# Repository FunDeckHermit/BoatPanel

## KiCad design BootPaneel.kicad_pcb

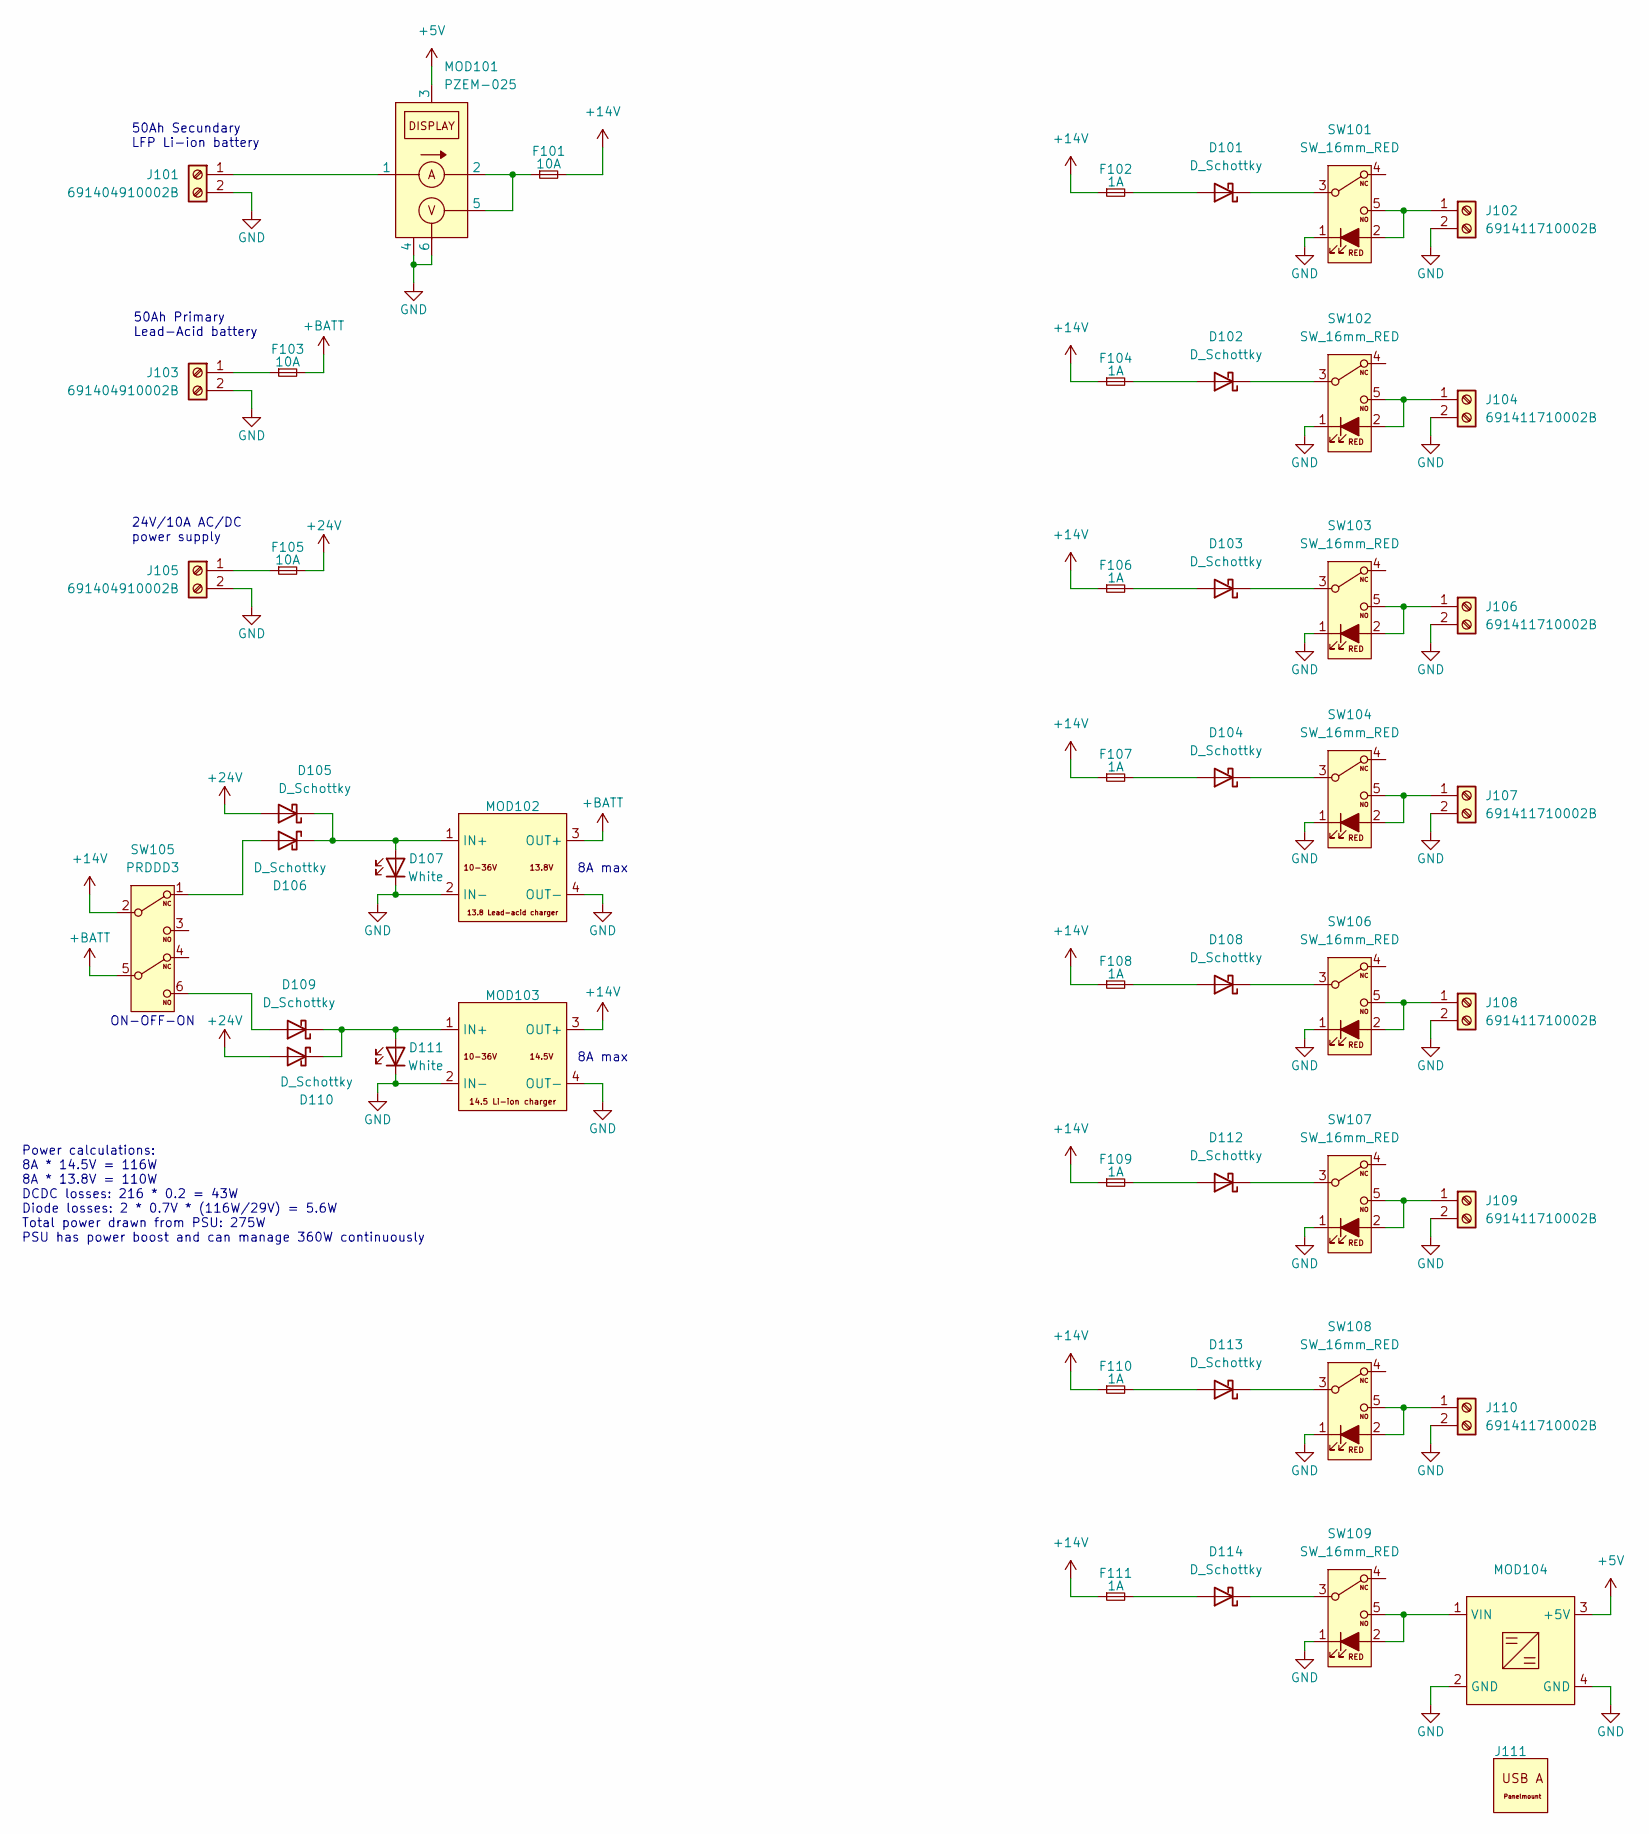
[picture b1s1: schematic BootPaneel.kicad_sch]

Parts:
D101, D102, D103, D104, D105, D106, D108, D109, D110, D112, D113, D114: D_Schottky; D_DO-201AD_P15.24mm_Horizontal
D107, D111: White; LED_Indictor-8mm
F101, F103, F105: 10A; FuseHolder_Regular
F102, F104, F106, F107, F108, F109, F110, F111: 1A; FuseHolder_Regular
J101, J103, J105: 691404910002B
J102, J104, J106, J107, J108, J109, J110: 691411710002B
J111: USBA-PanelMount
MOD101: PZEM-025; DISP_PZEM-025
MOD102, MOD103: MOD_DCDC_14.5V-CHG
MOD104: MOD_BUCK_5V3A
SW101, SW102, SW103, SW104, SW106, SW107, SW108, SW109: SW_16mm_RED; SW_16mm_ILUM
SW105: PRDDD3; SW_PRDDD3

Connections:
+5V: MOD101.3, MOD104.3 (+5V)
+14V: F101.2, F102.1, F104.1, F106.1, F107.1, F108.1, F109.1, F110.1, F111.1, MOD103.3 (OUT+), SW105.2 (C)
+24V: D105.2 (A), D110.2 (A), F105.2
+BATT: F103.2, MOD102.3 (OUT+), SW105.5 (C)
GND: D107.1 (K), D111.1 (K), J101.2, J102.2, J103.2, J104.2, J105.2, J106.2, J107.2, J108.2, J109.2, J110.2, MOD101.4, MOD101.6, MOD102.2 (IN-), MOD102.4 (OUT-), MOD103.2 (IN-), MOD103.4 (OUT-), MOD104.2 (GND), MOD104.4 (GND), SW101.1 (+), SW102.1 (+), SW103.1 (+), SW104.1 (+), SW106.1 (+), SW107.1 (+), SW108.1 (+), SW109.1 (+)
unnamed: D101.2 (A), F102.2
unnamed: D101.1 (K), SW101.3 (C)
unnamed: D102.2 (A), F104.2
unnamed: D102.1 (K), SW102.3 (C)
unnamed: D103.2 (A), F106.2
unnamed: D103.1 (K), SW103.3 (C)
unnamed: D104.2 (A), F107.2
unnamed: D104.1 (K), SW104.3 (C)
unnamed: D105.1 (K), D106.1 (K), D107.2 (A), MOD102.1 (IN+)
unnamed: D106.2 (A), SW105.1 (NC)
unnamed: D108.2 (A), F108.2
unnamed: D108.1 (K), SW106.3 (C)
unnamed: D109.2 (A), SW105.6 (NO)
unnamed: D109.1 (K), D110.1 (K), D111.2 (A), MOD103.1 (IN+)
unnamed: D112.2 (A), F109.2
unnamed: D112.1 (K), SW107.3 (C)
unnamed: D113.2 (A), F110.2
unnamed: D113.1 (K), SW108.3 (C)
unnamed: D114.2 (A), F111.2
unnamed: D114.1 (K), SW109.3 (C)
unnamed: F101.1, MOD101.2, MOD101.5
unnamed: J101.1, MOD101.1
unnamed: J102.1, SW101.2 (-), SW101.5 (NO)
unnamed: F103.1, J103.1
unnamed: J104.1, SW102.2 (-), SW102.5 (NO)
unnamed: F105.1, J105.1
unnamed: J106.1, SW103.2 (-), SW103.5 (NO)
unnamed: J107.1, SW104.2 (-), SW104.5 (NO)
unnamed: J108.1, SW106.2 (-), SW106.5 (NO)
unnamed: J109.1, SW107.2 (-), SW107.5 (NO)
unnamed: J110.1, SW108.2 (-), SW108.5 (NO)
unnamed: MOD104.1 (VIN), SW109.2 (-), SW109.5 (NO)

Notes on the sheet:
8A max
Power calculations: 8A * 14.5V = 116W 8A * 13.8V = 110W DCDC losses: 216 * 0.2 = 43W Diode losses: 2 * 0.7V * (116W/29V) = 5.6W Total power drawn from PSU: 275W PSU has power boost and can manage 360W continuously
24V/10A AC/DC power supply
ON-OFF-ON
50Ah Secundary LFP Li-ion battery
50Ah Primary Lead-Acid battery

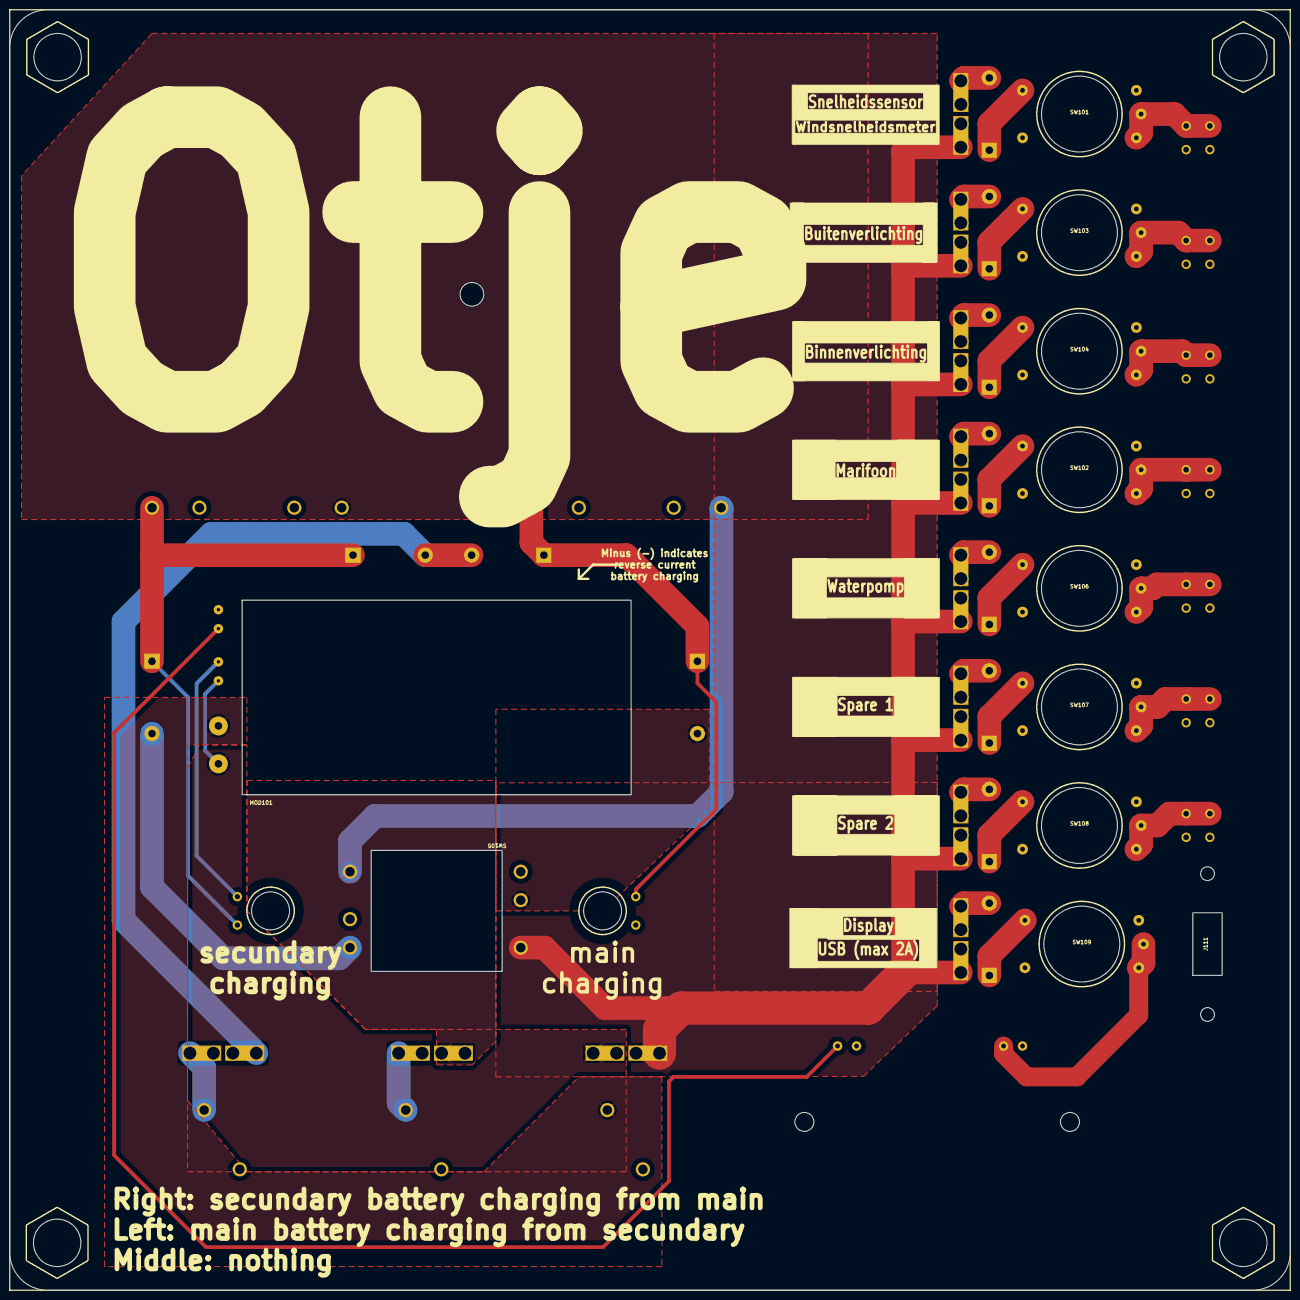
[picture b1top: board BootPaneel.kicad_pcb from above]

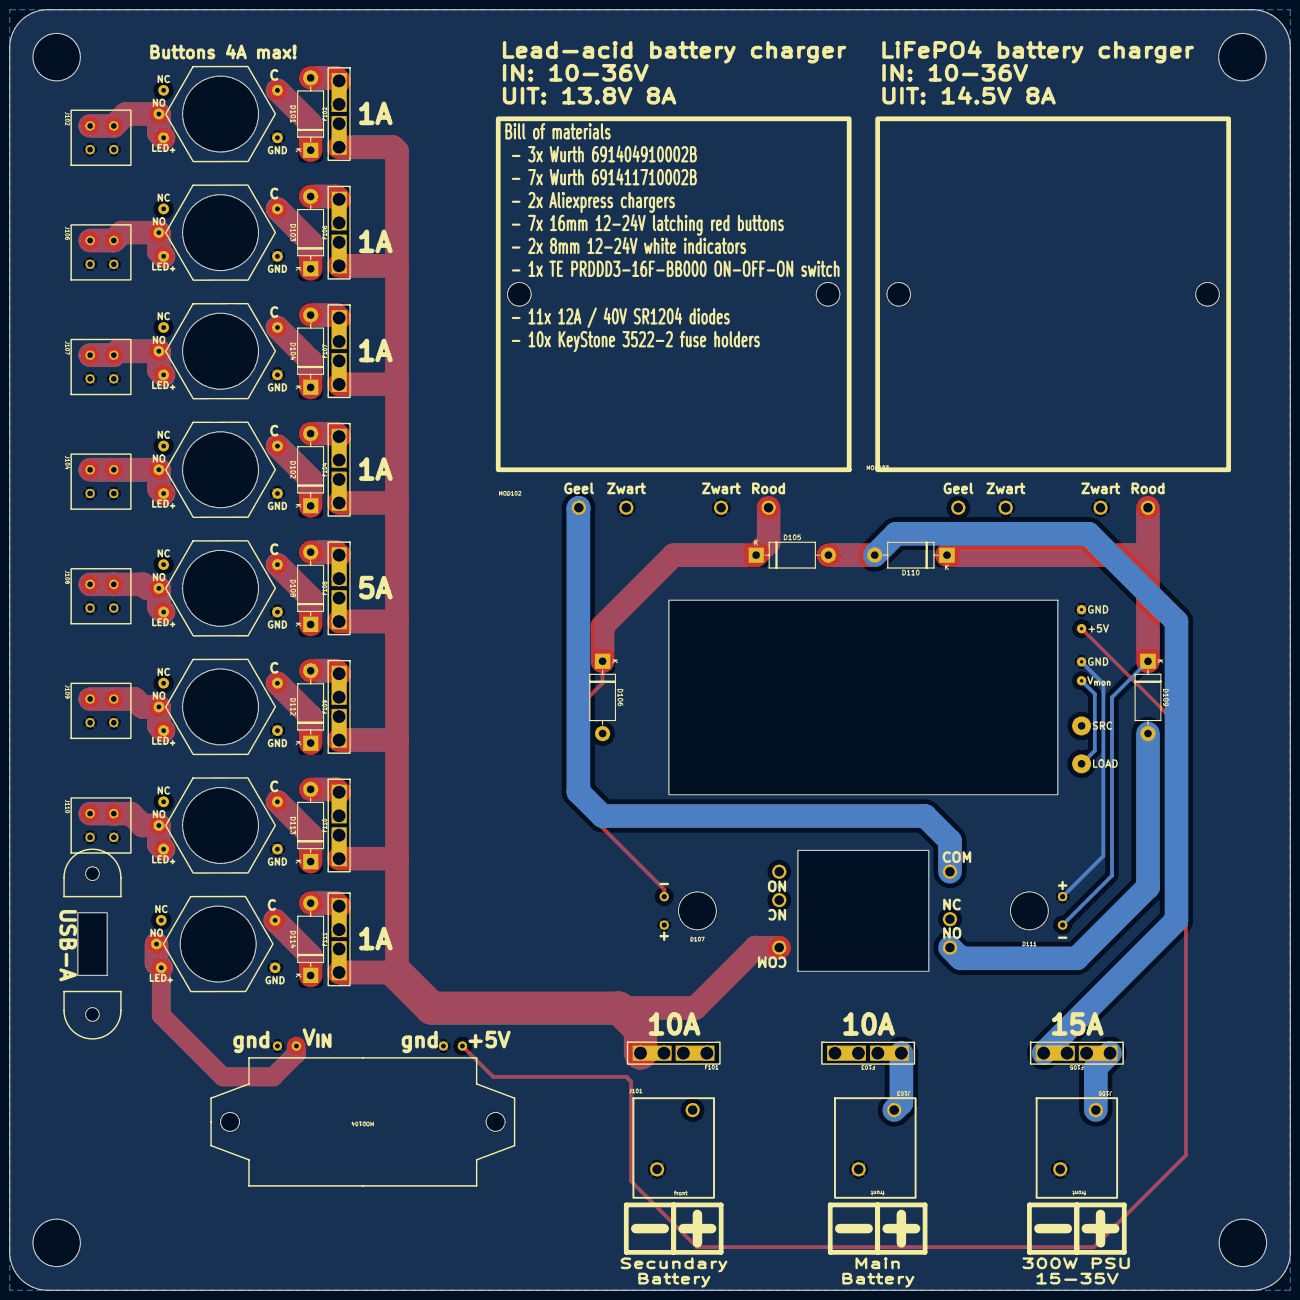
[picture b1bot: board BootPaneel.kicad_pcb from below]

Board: 2 copper layers, 270.0 x 270.0 mm, 49 parts (36 on the bottom side), 37 nets.
